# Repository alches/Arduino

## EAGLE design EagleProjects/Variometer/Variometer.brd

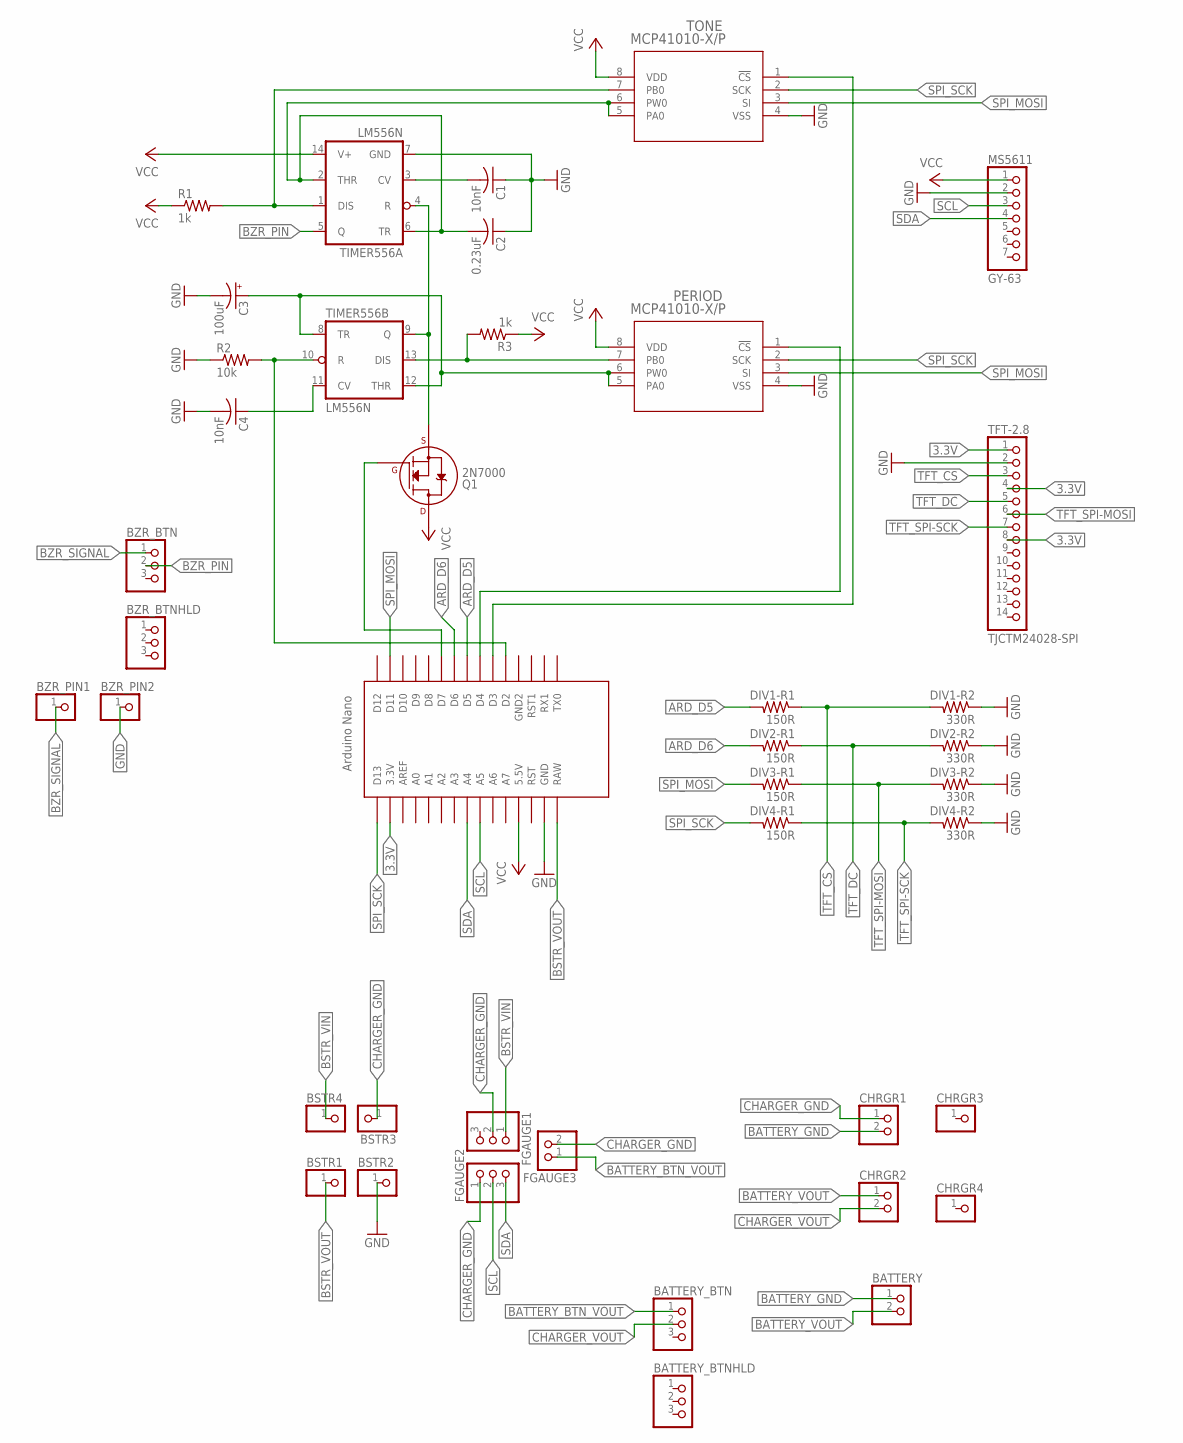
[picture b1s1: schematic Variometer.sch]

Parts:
BATTERY: PINHD-1X2; 1X02
BATTERY_BTN: PINHD-1X3; 1X03
BATTERY_BTNHLD: PINHD-1X3; 1X03
BSTR1, BSTR2, BSTR3, BSTR4: PINHD-1X1; 1X01
BZR_BTN: PINHD-1X3; 1X03
BZR_BTNHLD: PINHD-1X3; 1X03
BZR_PIN1, BZR_PIN2: PINHD-1X1; 1X01
C1, C4: 10nF; C025-024X044
C2: 0.23uF; C050-025X075
C3: 100uF; E2,5-7
CHRGR1, CHRGR2: PINHD-1X2; 1X02
CHRGR3, CHRGR4: PINHD-1X1; 1X01
DIV1-R1, DIV2-R1, DIV3-R1, DIV4-R1: 150R; R0805
DIV1-R2, DIV2-R2, DIV3-R2, DIV4-R2: 330R; R0805
FGAUGE1, FGAUGE2: PINHD-1X3; 1X03
FGAUGE3: PINHD-1X2; 1X02
MS5611: GY-63; 1X07
PERIOD: MCP41010-X/P; PDIP8_300MC
Q1: 2N7000; TO-92
R1, R3: 1k; R0805
R2: 10k; R0805
TFT-2.8: TJCTM24028-SPI; 1X14
TIMER556: LM556N; DIL14
TONE: MCP41010-X/P; PDIP8_300MC
U$1: NANO

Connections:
3.3V: TFT-2.8.1, TFT-2.8.4, TFT-2.8.8, U$1.3.3V
ARD_D5: DIV1-R1.2, U$1.D5
ARD_D6: DIV2-R1.2, U$1.D6
BATTERY_BTN_VOUT: BATTERY_BTN.1, FGAUGE3.1
BATTERY_GND: BATTERY.1, CHRGR1.2
BATTERY_VOUT: BATTERY.2, CHRGR2.1
BSTR_VIN: BSTR4.1, FGAUGE1.1
BSTR_VOUT: BSTR1.1, U$1.RAW
BZR_PIN: BZR_BTN.2, TIMER556.5 (Q)
BZR_SIGNAL: BZR_BTN.1, BZR_PIN1.1
CHARGER_GND: BSTR3.1, CHRGR1.1, FGAUGE1.2, FGAUGE2.1, FGAUGE3.2
CHARGER_VOUT: BATTERY_BTN.2, CHRGR2.2
GND: BSTR2.1, BZR_PIN2.1, C1.1, C2.1, C3.-, C4.2, DIV1-R2.1, DIV2-R2.1, DIV3-R2.1, DIV4-R2.1, MS5611.2, PERIOD.4 (VSS), R2.1, TFT-2.8.2, TIMER556.7 (GND), TONE.4 (VSS), U$1.GND
unnamed: C2.2, TIMER556.2 (THR), TIMER556.6 (TR), TONE.5 (PA0), TONE.6 (PW0)
unnamed: C1.2, TIMER556.3 (CV)
unnamed: Q1.1 (S), TIMER556.4 (R), TIMER556.9 (Q)
unnamed: Q1.2 (G), U$1.D7
unnamed: C4.1, TIMER556.11 (CV)
unnamed: TONE.1 (!CS), U$1.D3
unnamed: PERIOD.7 (PB0), R3.2, TIMER556.13 (DIS)
unnamed: R2.2, TIMER556.10 (R), U$1.D2
unnamed: R1.2, TIMER556.1 (DIS), TONE.7 (PB0)
unnamed: C3.+, PERIOD.5 (PA0), PERIOD.6 (PW0), TIMER556.8 (TR), TIMER556.12 (THR)
unnamed: PERIOD.1 (!CS), U$1.D4
SCL: FGAUGE2.2, MS5611.3, U$1.A5
SDA: FGAUGE2.3, MS5611.4, U$1.A4
SPI_MOSI: DIV3-R1.2, PERIOD.3 (SI), TONE.3 (SI), U$1.D11
SPI_SCK: DIV4-R1.2, PERIOD.2 (SCK), TONE.2 (SCK), U$1.D13
TFT_CS: DIV1-R1.1, DIV1-R2.2, TFT-2.8.3
TFT_DC: DIV2-R1.1, DIV2-R2.2, TFT-2.8.5
TFT_SPI-MOSI: DIV3-R1.1, DIV3-R2.2, TFT-2.8.6
TFT_SPI-SCK: DIV4-R1.1, DIV4-R2.2, TFT-2.8.7
VCC: MS5611.1, PERIOD.8 (VDD), Q1.3 (D), R1.1, R3.1, TIMER556.14 (V+), TONE.8 (VDD), U$1.5V (5.5V)

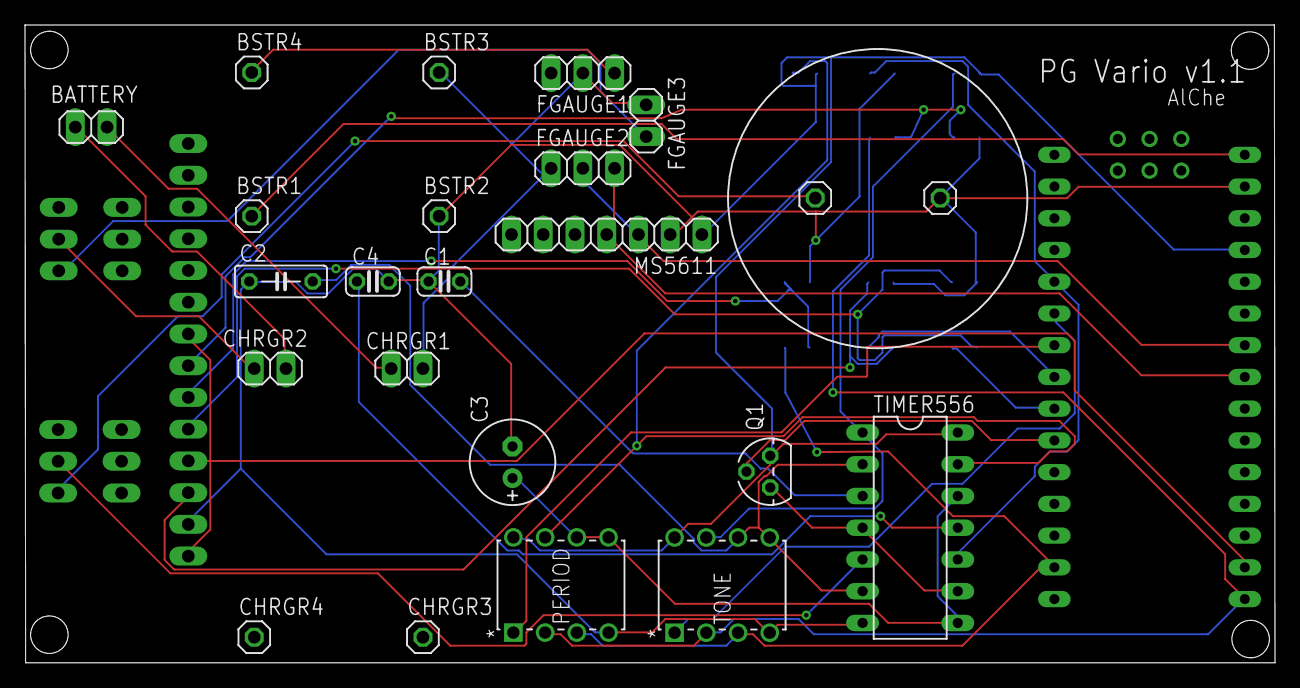
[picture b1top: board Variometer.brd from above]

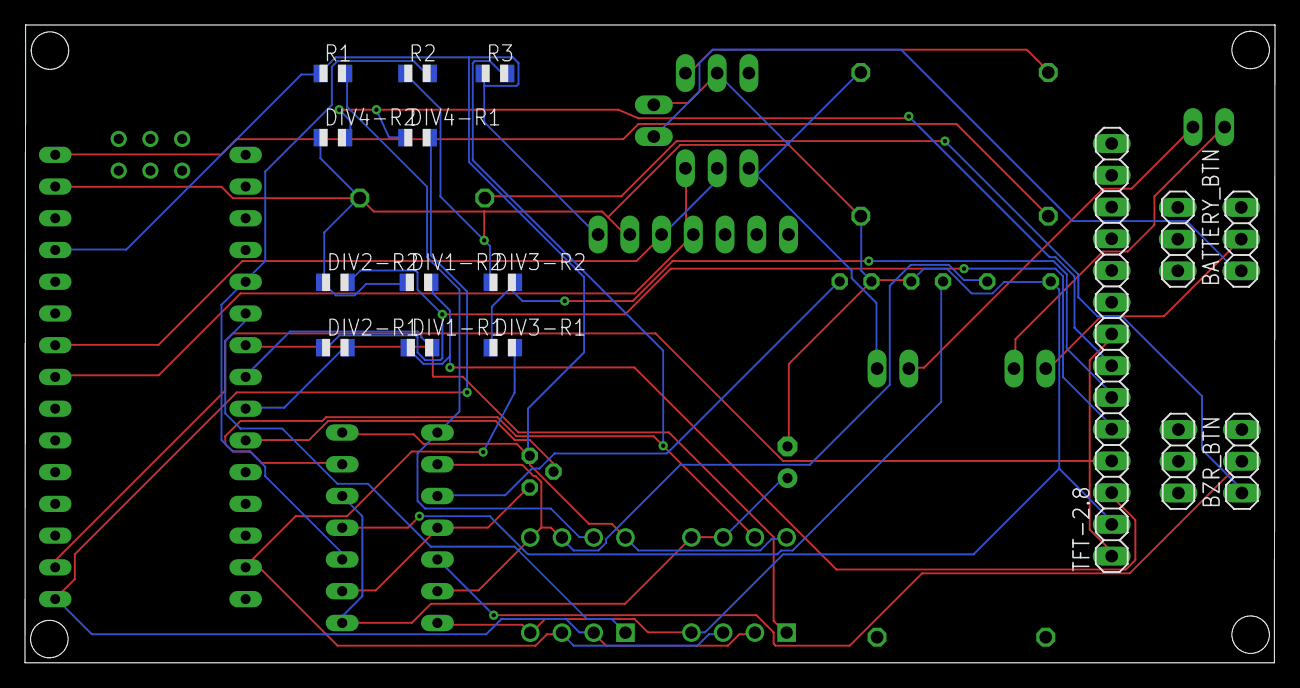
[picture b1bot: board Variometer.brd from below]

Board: 2 copper layers, 100.0 x 51.0 mm, 40 parts (16 on the bottom side), 33 nets.

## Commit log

2017-03-10 initial
2017-04-06 Cleaned repo
2017-04-06 Added home repo
2017-04-06 Added MS5611 lib
2017-04-19 Changes20.04.2017
2017-04-23 Added kalman, reverted to adafruit lib
2017-05-03 Designed bar
2017-05-20 Screen work
2017-05-30 Battery measurement
2018-01-12 EagleLibraries stored
2018-02-25 Added Eagle project
2018-04-08 Eagle Project v1.1
    Fixed pcb bugs in v1.0 version
